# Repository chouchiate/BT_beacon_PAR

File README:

- (Keil uvision) Beacon Demo Firmware PAR2860 BLE Module
- (Kicad) Module Breakout board

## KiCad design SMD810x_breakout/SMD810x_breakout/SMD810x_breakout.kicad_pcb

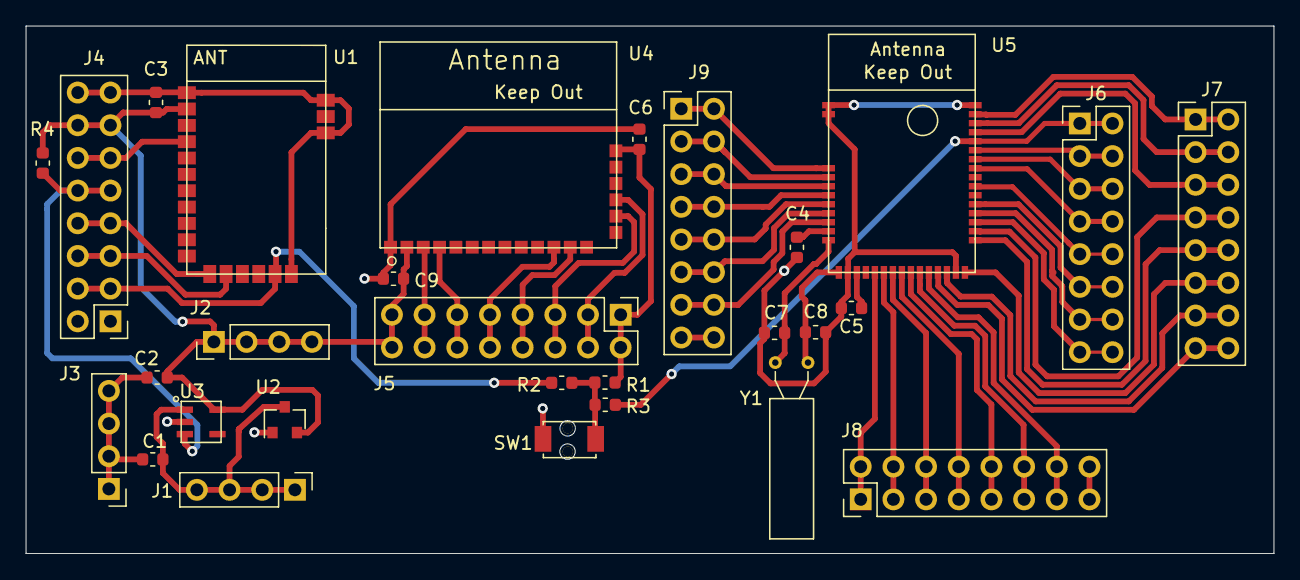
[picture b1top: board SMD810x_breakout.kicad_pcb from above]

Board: 2 copper layers, 97.0 x 41.0 mm, 29 parts (0 on the bottom side), 53 nets.

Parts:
C1, C2: 10uF; C_0603_1608Metric
C3, C4, C5, C6, C7, C8, C9: C_Small; C_0603_1608Metric
J1, J2, J3: Conn_01x04; PinHeader_1x04_P2.54mm_Vertical
J4, J5, J6, J7, J8, J9: Conn_02x08_Odd_Even; PinHeader_2x08_P2.54mm_Vertical
R1, R2, R3, R4: R_US; R_0603_1608Metric
SW1: SW_Push; 1185-TCSW
U1: SMD810X_S0X; SMD810X
U2: EC6209-3V3; SOT-23
U3: APL5320
U4: SMD2860-P095-1x; SMD2860-P095-1X
U5: GW_BT52832_QFxx; GW-BT52832QF-xx
Y1: Crystal_Small; Crystal_AT310_D3.0mm_L10.0mm_Horizontal

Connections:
3V3: C2.1, C3.1, C9.1, J2.1, J2.2, J2.3, J2.4, J4.13, J4.14, J5.15, J5.16, R4.2, U1.2, U2.2, U3.5, U4.2
5V: C1.1, J1.1, J1.2, J1.3, J1.4, U2.3, U3.1
AIN4: J9.7, J9.8, U5.6
AIN5: J9.9, J9.10, U5.7
AIN6: J9.11, J9.12, U5.8
AIN7: J9.13, J9.14, U5.9
DIO_02: J8.1, J8.2, U5.16
DIO_03: J8.3, J8.4, U5.17
DIO_04: J8.5, J8.6, U5.18
DIO_05: J8.7, J8.8, U5.19
DIO_06: J8.9, J8.10, U5.20
DIO_07: J8.11, J8.12, U5.21
DIO_08: J8.13, J8.14, U5.22
DIO_11: J7.11, J7.12, U5.26
DIO_12: J7.9, J7.10, U5.27
DIO_13: J7.7, J7.8, U5.28
DIO_22: J7.5, J7.6, U5.39
DIO_23: J7.3, J7.4, U5.40
DIO_24: J7.1, J7.2, U5.41
DIO_25: J9.1, J9.2, U5.3
DIO_26: J9.3, J9.4, U5.4
DIO_27: J9.5, J9.6, U5.5
EN: J4.11, J4.12, U1.4
GND: C1.2, C2.2, C3.2, C4.2, C5.2, C6.2, C7.2, C8.2, C9.2, J3.1, J3.2, J3.3, J3.4, J4.15, J4.16, SW1.1, U1.1, U1.17, U1.18, U1.20, U2.1, U3.2, U4.1, U5.1, U5.2, U5.13, U5.25, U5.42
GPIO0: J5.11, J5.12, U4.4
GPIO1: J5.13, J5.14, U4.3
LDO_EN: J4.9, J4.10, R4.1, U3.3
MCU_RX: J5.5, J5.6, U4.15
MCU_TX: J5.3, J5.4, U4.16
NFC0: J7.15, J7.16, U5.23
NFC1: J7.13, J7.14, U5.24
unnamed: C4.1, U5.10
unnamed: C5.1, U5.14
unnamed: J4.1, J4.2
unnamed: J8.15, J8.16
unnamed: J9.15, J9.16
unnamed: R1.2, R2.2, R3.2, SW1.2
RESETn: C6.1, J5.1, J5.2, R1.1, U4.19
SWDCLK: J5.7, J5.8, U4.12
SWDCLK_NORDIC: J6.5, J6.6, U5.36
SWDIO: J5.9, J5.10, U4.11
SWDIO_NORDIC: J6.7, J6.8, U5.35
TRACE_CLK: J6.3, J6.4, U5.37
TRACE_D0: J6.9, J6.10, U5.33
TRACE_D1: J6.11, J6.12, U5.31
TRACE_D2: J6.13, J6.14, U5.30
TRACE_D3: J6.15, J6.16, U5.29
UART_RX: J4.7, J4.8, U1.12
UART_TX: J4.5, J4.6, U1.13
XL1_32_768: C7.1, U5.11, Y1.1
XL2_32_768: C8.1, U5.12, Y1.2
nRESET: J4.3, J4.4, R2.1, U1.16
nRESET_NORDIC: J6.1, J6.2, R3.1, U5.38

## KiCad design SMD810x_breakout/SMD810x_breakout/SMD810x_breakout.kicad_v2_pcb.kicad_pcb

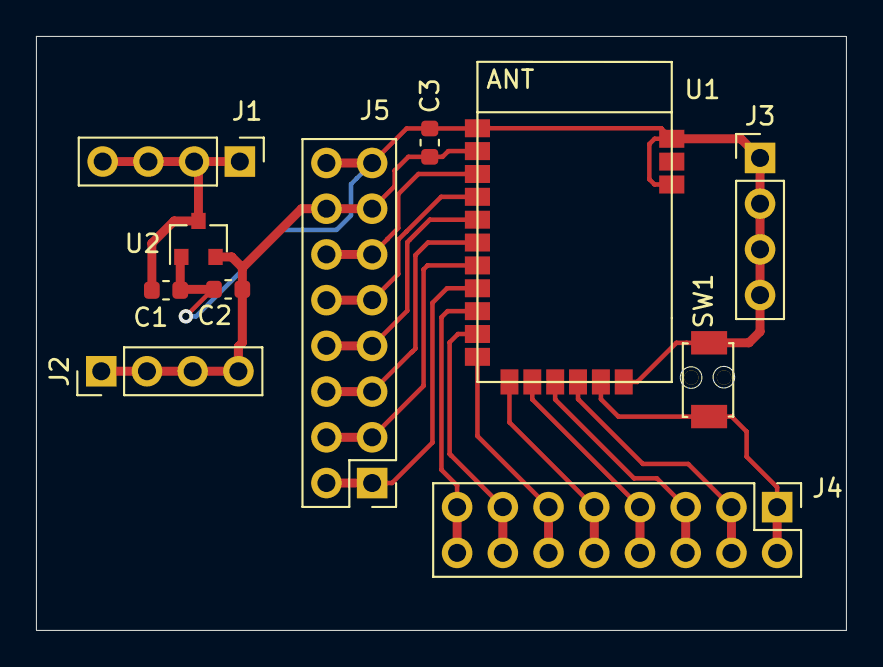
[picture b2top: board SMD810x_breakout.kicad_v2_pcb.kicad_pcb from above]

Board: 2 copper layers, 45.0 x 33.0 mm, 11 parts (0 on the bottom side), 17 nets.

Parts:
C1, C2: 10uF; C_0603_1608Metric
C3: C_Small; C_0603_1608Metric
J1, J2, J3: Conn_01x04; PinHeader_1x04_P2.54mm_Vertical
J4, J5: Conn_02x08_Odd_Even; PinHeader_2x08_P2.54mm_Vertical
SW1: SW_Push; 1185-TCSW
U1: SMD810X_S0X; SMD810X
U2: EC6209-3V3; SOT-23

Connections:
3V3: C2.1, C3.1, J2.1, J2.2, J2.3, J2.4, J5.13, J5.14, U1.2, U2.2
5V: C1.1, J1.1, J1.2, J1.3, J1.4, U2.3
/P0_0: J5.11, J5.12, U1.3
/P0_2: J5.7, J5.8, U1.5
/P0_3: J5.5, J5.6, U1.6
/P0_4: J5.3, J5.4, U1.7
/P0_7: J4.3, J4.4, U1.15
/P1_4: J5.1, J5.2, U1.8
/P1_5: J4.15, J4.16, U1.9
/P1_6: J4.13, J4.14, U1.10
/P1_7: J4.11, J4.12, U1.11
/P3_2: J4.5, J4.6, U1.14
EN: J5.9, J5.10, U1.4
GND: C1.2, C2.2, C3.2, J3.1, J3.2, J3.3, J3.4, J5.15, J5.16, SW1.1, U1.1, U1.17, U1.18, U1.20, U2.1
UART_RX: J4.9, J4.10, U1.12
UART_TX: J4.7, J4.8, U1.13
nRESET: J4.1, J4.2, SW1.2, U1.16

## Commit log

2024-08-29 add uvprojx
